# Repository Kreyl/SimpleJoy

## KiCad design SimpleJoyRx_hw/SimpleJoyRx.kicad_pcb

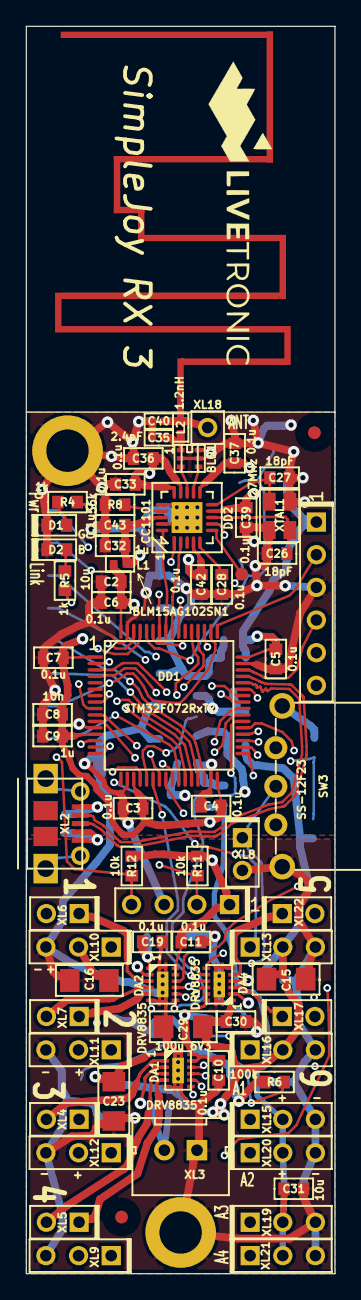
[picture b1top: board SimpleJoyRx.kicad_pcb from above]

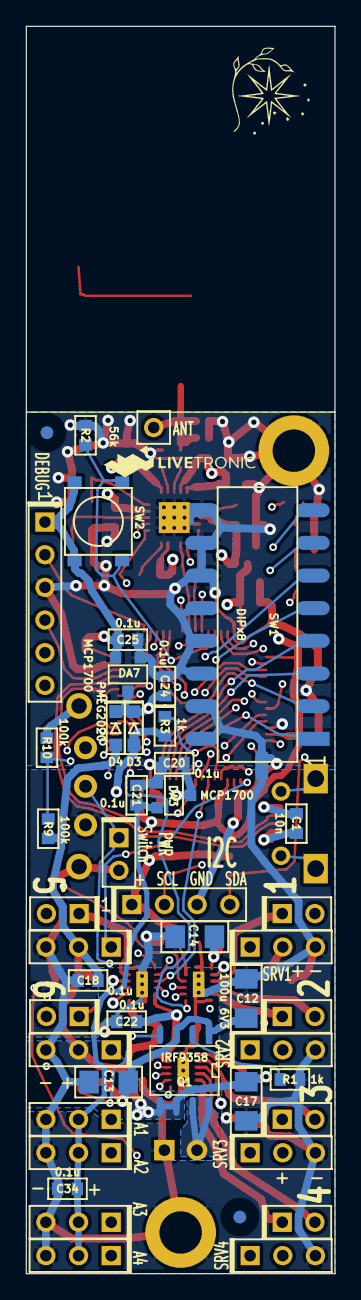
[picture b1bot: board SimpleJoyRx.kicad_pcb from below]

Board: 4 copper layers, 24.0 x 97.0 mm, 105 parts (29 on the bottom side), 82 nets.

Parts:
ANT1: ANT_PCB_MONO; ANT_868_24x30
BLN1: BALUN868JOHANSON; BALUN_JOHANSON868
C1, C8: 10n; CAP_0603
C2, C31: 10u; CAP_0603
C3, C4, C5, C6, C7, C10, C11, C18, C19, C20, C21, C22, C24, C25, C28, C30, C33, C34, C36, C37, C39, C42, C43: 0.1u; CAP_0603
C9, C32: 1u; CAP_0603
C12, C13, C14, C15, C16, C17, C23, C29: 100u 6V3; CAP_1206
C26, C27: 18pF; CAP_0603
C35: 2.4pF; CAP_0402
C40: DoNotMount; CAP_0402
D1: L-C191KGCT; LED_0603
D2: L-C191LBCT; LED_0603
D3, D4: PMEG2020; SOD323
DA1, DA2, DA4: DRV8835; WSON12
DA3, DA7: MCP1700; SOT23-3A
DD1: STM32F072RxTx; LQFP64
DD2: CC1101; QFN20
F1: Fuse0R; FuseShorted
HOLE1, HOLE2: HOLE_METALLED; Hole3d3_out5d5mm
L1: BLM15AG102SN1; IND_0402
L2: 1.2nH; IND_0402
Logo1: Logo; Ostranna_8x8
Logo2: Logo; Livetronic27x9
Logo3: Logo; Livetronic13x4
Q1: IRF9358; SO8_150MIL
R1, R3, R4, R5: 1k; RES_0603
R2, R8: 56k; RES_0603
R6, R9, R10: 100k; RES_0603
R11, R12: 10k; RES_0603
RP1, RP2, RP3, RP4: REFPOINT; REF_POINT_1MM
SW1: DIPx8; DIP_SMD_X8
SW2: IT-1187A; BTN_4x4_SMD
SW3: SS-12F23; SW_SS-12F23
TP1: TESTPOINT; TESTPOINT_1MM
XL1: CONN_6; PLS-6
XL2: USB_MICRO; USBmicro_MOLEX_1050170001
XL3: CONN_2; W02_Pitch_2d54
XL4, XL5, XL6, XL7, XL8, XL17, XL22: PLS2; PLS-2
XL9, XL10, XL11, XL12, XL13, XL15, XL16, XL19, XL20, XL21: PLS3; PLS-3
XL14: CONN_4; PLS-4
XL18: CONN_1; PLS-1Rnd
XTAL1: 27MHz; 03225C4

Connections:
+3.3V: C2.1, C3.1, C4.1, C5.1, C6.1, C7.1, C8.1, C9.1, C10.2, C11.2, C22.2, C25.1, DA1.11, DA1.12, DA2.11, DA2.12, DA4.11, DA4.12, DA7.2, DD1.1, DD1.13, DD1.19, DD1.32, DD1.48, DD1.64, L1.2, R11.1, R12.1, SW2.2, XL1.1, XL14.1
+BATT: C12.2, C13.2, Q1.1, Q1.3, R6.2
/5V_USB: C1.2, D3.A, R3.1, XL2.1
/A1: DD1.10, XL15.1
/A2: DD1.11, XL20.1
/A3: DD1.24, XL19.1
/A4: DD1.25, XL21.1
/ANT1: BLN1.1, C35.1, L2.2
/ANT2: ANT1.1, C40.1, L2.1, XL18.1
/BAT_MEAS: DD1.14, R9.1, R10.2
/CC_CS: DD1.28, DD2.7
/CC_GDO0: DD1.27, DD2.6, TP1.1
/CC_MISO: DD1.56, DD2.2
/CC_MOSI: DD1.57, DD2.20
/CC_SCK: DD1.55, DD2.1
/D+: DD1.45, XL2.3
/D-: DD1.44, XL2.2
/DIP1: DD1.26, SW1.1
/DIP2: DD1.50, SW1.2
/DIP3: DD1.29, SW1.3
/DIP4: DD1.30, SW1.4
/DIP5: DD1.33, SW1.5
/DIP6: DD1.34, SW1.6
/DIP7: DD1.35, SW1.7
/DIP8: DD1.36, SW1.8
/DIR1: DA2.10, DD1.51
/DIR2: DA2.8, DD1.52
/DIR3: DA1.10, DD1.53
/DIR4: DA1.8, DD1.2
/DIR5: DA4.10, DD1.3
/DIR6: DA4.8, DD1.4
/MCU_PWR: C20.1, C24.1, D3.C, D4.C, DA3.3, DA7.3
/MOTORA1: DA2.2, XL6.2
/MOTORA2: DA2.3, XL6.1
/MOTORB1: DA2.4, XL7.2
/MOTORB2: DA2.5, XL7.1
/MOTORC1: DA1.2, XL4.2
/MOTORC2: DA1.3, XL4.1
/MOTORD1: DA1.4, XL5.2
/MOTORD2: DA1.5, XL5.1
/MOTORE1: DA4.2, XL17.2
/MOTORE2: DA4.3, XL17.1
/MOTORF1: DA4.4, XL22.2
/MOTORF2: DA4.5, XL22.1
/PRE_BAT_PWR: Q1.7, Q1.8, XL3.2
/PWM1: DA2.9, DD1.37
/PWM2: DA2.7, DD1.38
/PWM3: DA1.9, DD1.39
/PWM4: DA1.7, DD1.40
/PWM5: DA4.9, DD1.22
/PWM6: DA4.7, DD1.23
/RF1: BLN1.4, DD2.12
/RF2: BLN1.3, DD2.13
/SCL: DD1.61, R11.2, XL14.2
/SDA: DD1.62, R12.2, XL14.4
/SRV1: DD1.41, XL10.1
/SRV2: DD1.42, XL11.1
/SRV3: DD1.43, XL12.1
/SRV4: DD1.16, XL9.1
/SRV5: DD1.17, XL13.1
/SRV6: DD1.20, XL16.1
/SWCLK: DD1.49, XL1.2
/SWDIO: DD1.46, XL1.4
/UART_RX: DD1.59, XL1.6
/UART_TX: DD1.58, XL1.5
GND: BLN1.2, BLN1.5, BLN1.6, C1.1, C2.2, C3.2, C4.2, C5.2, C6.2, C7.2, C8.2, C9.2, C20.2, C21.2, C24.2, C25.2, C26.2, C27.2, C28.1, C32.1, C33.2, C35.2, C36.2, C37.2, C39.2, C40.2, C42.2, C43.2, D1.C, D2.C, DA3.1, DA7.1, DD1.12, DD1.18, DD1.31, DD1.47, DD1.63, DD2.16, DD2.19, DD2.PAD, F1.1, HOLE1.H, R2.2, R8.2, SW1.9, SW1.10, SW1.11, SW1.12, SW1.13, SW1.14, SW1.15, SW1.16, XL1.3, XL2.4, XL2.5, XL14.3, XTAL1.H
GNDPWR: C10.1, C11.1, C12.1, C13.1, C14.1, C15.1, C16.1, C17.1, C18.1, C19.1, C22.1, C23.1, C29.1, C30.1, C31.2, C34.1, DA1.6, DA1.PAD, DA2.6, DA2.PAD, DA4.6, DA4.PAD, F1.2, HOLE2.H, R1.2, R10.1, SW3.1, SW3.H, XL3.1, XL8.2, XL9.3, XL10.3, XL11.3, XL12.3, XL13.3, XL15.3, XL16.3, XL19.3, XL20.3, XL21.3
unnamed: C26.1, DD2.8, XTAL1.1
unnamed: C27.1, DD2.10, XTAL1.2
unnamed: C28.2, DD2.5
unnamed: D1.A, R4.1
unnamed: D2.A, R5.1
unnamed: DD1.8, R4.2
unnamed: DD1.9, R5.2
unnamed: DD1.21, R3.2
unnamed: DD1.60, R2.1, SW2.1
unnamed: DD2.17, R8.1
unnamed: Q1.2, R1.1
unnamed: Q1.4, R6.1, SW3.2, XL8.1
PwrUnst: C14.2, C15.2, C16.2, C17.2, C18.2, C19.2, C23.2, C29.2, C30.2, D4.A, DA1.1, DA2.1, DA4.1, Q1.5, Q1.6, R9.2, XL9.2, XL10.2, XL11.2, XL12.2, XL13.2, XL16.2
VAA: C21.1, C31.1, C34.2, DA3.2, XL15.2, XL19.2, XL20.2, XL21.2
VCC: C32.2, C33.1, C36.1, C37.1, C39.1, C42.1, C43.1, DD2.4, DD2.9, DD2.11, DD2.14, DD2.15, DD2.18, L1.1

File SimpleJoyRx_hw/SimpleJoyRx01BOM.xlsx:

Reference | Value | Footprint | Quantity | SolderPoints | Price | PN | URL | Info | SolderPointsDip | Color | Sum
ANT1 | ANT_PCB_MONO | Radio:ANT_868_24x30 | 1 | 0 | 0
BLN1 | BALUN868JOHANSON | Radio:BALUN_JOHANSON868 | 1 | 6 | 45 | 0896BM15A0001E | http://onelec.ru/products/0896bm15a0001e-52ab3408-7c12-4b8c-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
C2 | 10u | Capacitors:CAP_0603 | 1 | 2 | 4
C26 C27 | 18pF | Capacitors:CAP_0603 | 2 | 2 | 0.5
C10 C11 C18 C19 C20 C21 C24 C25 C28 C3 C31 C33 C36 C37 C39 C4 C41 C42 C43 C5 C6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 | 0.1u | Capacitors:CAP_0603 | 22 | 2 | 0.5
C35 | 2.4pF | Capacitors:CAP_0402 | 1 | 2 | 0.5
C12 C13 C14 C15 C16 C17 C30 C38 | 100u 6V3 | Capacitors:CAP_1206 | 8 | 2 | 7 | CL31A107MQHNNNE
C40 | DoNotMount | Capacitors:CAP_0402 | 1 | 2 | 0.5
C1 C8 | 10n | Capacitors:CAP_0603 | 2 | 2 | 0.5
C32 C9 | 1u | Capacitors:CAP_0603 | 2 | 2 | 0.5
D1 | L-C191KGCT | LEDs:LED_0603 | 1 | 2 | 2.2000000000000002 | L-C191KGCT | http://onelec.ru/products/l-c191kgct |  |  | Green
D2 | L-C191LBCT | LEDs:LED_0603 | 1 | 2 | 2.4 | L-C191LBCT | http://onelec.ru/products/l-c191lbct |  |  | Blue
D3 D4 D5 D6 | PMEG2020 | Diodes:SOD323 | 4 | 2 | 5.5 | PMEG2020EJ.115 | https://www.terraelectronica.ru/catalog_info.php?CODE=192057 | 2A 20V Vf=525mV
DA1 DA2 | DRV8835 | QFN_DFN:WSON12 | 2 | 13 | 95 | DRV8835DSSR | http://onelec.ru/products/drv8835dssr
DA3 DA7 | MCP1700 | SOT:SOT23-3A | 2 | 3 | 20 | MCP1700T-3302E/TT
DD1 | STM32F072RxTx | LQFP_TQFP:LQFP64 | 1 | 64 | 170 | stm32f072R8t6 | http://
DD2 | CC1101 | QFN_DFN:QFN20 | 1 | 21 | 140 |  | http://
F1 | Fuse0R | PCB:FuseShorted | 1 | 1 | 0
HOLE1 HOLE2 | HOLE_METALLED | PCB:Hole3d3_out5d5mm | 2 | 0 | 0
L1 | BLM15AG102SN1 | Inductors:IND_0402 | 1 | 2 | 1
L2 | 1.2nH | Inductors:IND_0402 | 1 | 2 | 4
Logo1 | Logo | Pictures:Ostranna_8x8 | 1 | 0 | 0
Logo2 | Logo | Pictures:Livetronic27x9 | 1 | 0 | 0
Logo3 | Logo | Pictures:Livetronic13x4 | 1 | 0 | 0
Q1 | IRF9358 | SO_DIL_TSSOP:SO8_150MIL | 1 | 8 | 29 |  | http://onelec.ru/products/irf9358pbf-dd012426-33d8-429e-9c6a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
Q2 | 2N7002 | SOT:SOT23-3 | 1 | 3 | 1.6
Q3 Q4 | IRLML0030 | SOT:SOT23-3 | 2 | 3 | 7.5 | IRLML0030TRPBF | https://www.terraelectronica.ru/catalog.php?ID=349&search=irlml0030
R1 R3 R4 R5 | 1k | Resistors:RES_0603 | 4 | 2 | 0.5
R10 R6 R7 R9 | 100k | Resistors:RES_0603 | 4 | 2 | 0.5
R11 R12 R2 R8 | 56k | Resistors:RES_0603 | 4 | 2 | 0.5
RP1 RP2 RP3 RP4 | REFPOINT | PCB:REF_POINT_1MM | 4 | 0 | 0
SW1 | DIPx8 | BtnsSwitches:DIP_SMD_X8 | 1 | 16 | 27 |  | http://www.zip-2002.ru/kommutatsiya/dip_pereklyuchateli/7128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
SW2 | IT-1187A | BtnsSwitches:BTN_4x4_SMD | 1 | 4 | 4 | IT-1187A
SW3 | 1P2T | BtnsSwitches:SW_SS-1P2T | 1 | 3 | 10
TP1 | TESTPOINT | PCB:TESTPOINT_1MM | 1 | 0 | 0
U1 | USBLC6 | SOT:SOT23-6 | 1 | 6 | 9 | USBLC6-2SC6 | https://www.terraelectronica.ru/catalog_info.php?CODE=244787
XL1 | CONN_6 | Connectors:PLS-6 | 1 | 6 | 1
XL10 XL11 XL12 XL13 XL15 XL16 XL19 XL20 XL21 XL9 | PLS3 | Connectors:PLS-3 | 10 | 3 | 1
XL14 XL17 XL4 XL5 XL6 XL7 XL8 | PLS2 | Connectors:PLS-2 | 7 | 2 | 0.5 |  |  |  | 2
XL18 | CONN_1 | Connectors:PLS-1Rnd | 1 | 0 | 0
XL2 | USB_MICRO | Connectors:USBmicro_MOLEX_1050170001 | 1 | 9 | 46 | 47491-0001
XL3 | CONN_2 | Connectors:W02_Pitch_2d54 | 1 | 2 | 2
XTAL1 | 27MHz | Quartz:03225C4 | 1 | 4 | 15
Печатная плата |  |  | 1 |  | 155 | 155
 |  |  | Итого | 209 |  | 155

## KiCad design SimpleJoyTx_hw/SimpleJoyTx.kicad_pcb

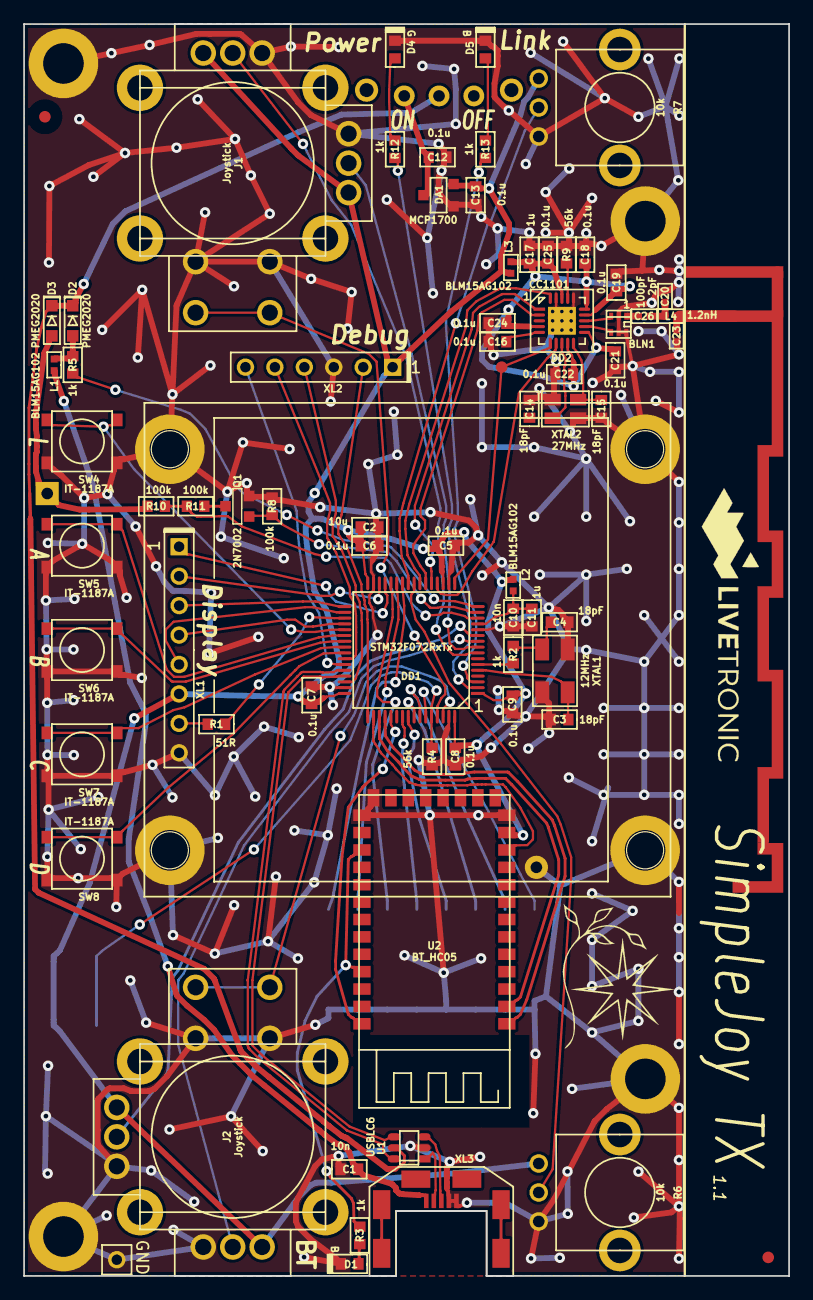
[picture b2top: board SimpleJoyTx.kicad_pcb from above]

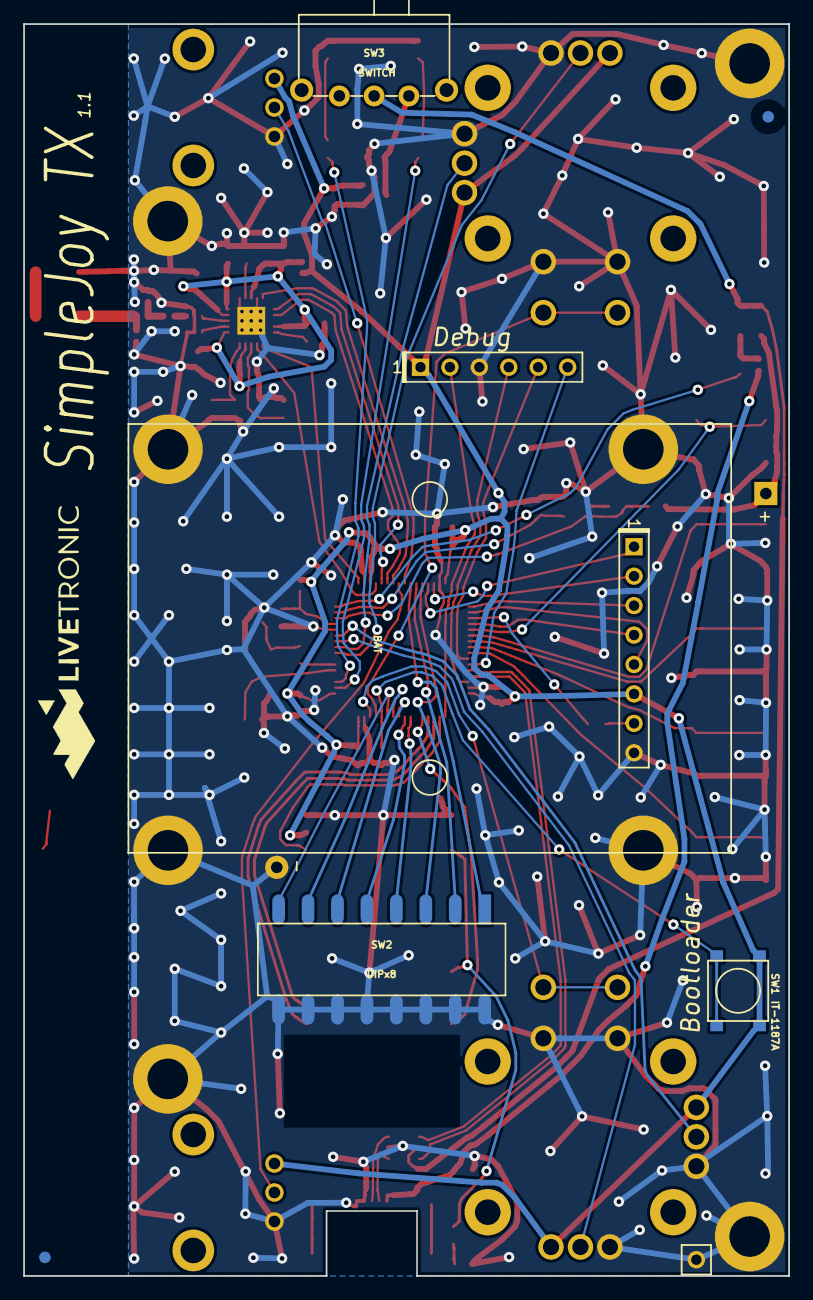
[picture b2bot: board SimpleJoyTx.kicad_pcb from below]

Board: 2 copper layers, 66.0 x 108.0 mm, 89 parts (7 on the bottom side), 77 nets.

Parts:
ANT1: ANT_PCB_MONO_2PIN; ANT_868_IFA_SIMPLEJOY
B1: BAT; BATTERY_AAA_X3
BLN1: BALUN868JOHANSON; BALUN_JOHANSON868
C1, C10: 10n; CAP_0603
C2: 10u; CAP_0603
C3, C4, C14, C15: 18pF; CAP_0603
C5, C6, C7, C8, C9, C12, C13, C16, C18, C19, C21, C22, C24, C25: 0.1u; CAP_0603
C11, C17: 1u; CAP_0603
C20: 2pF; CAP_0402
C23: DoNotMount; CAP_0402
C26: 100pF; CAP_0402
D1, D5: L-C191LBCT; LED_0603
D2, D3: PMEG2020; SOD323
D4: L-C191KGCT; LED_0603
DA1: MCP1700; SOT23-3A
DD1: STM32F072RxTx; LQFP64
DD2: CC1101; QFN20
HOLE1, HOLE2, HOLE3, HOLE4, HOLE5, HOLE6, HOLE7, HOLE8: HOLE_METALLED; Hole3_5_out6mm
J1, J2: Joystick
L1, L2, L3: BLM15AG102; IND_0402
L4: 1.2nH; IND_0402
Logo1: Logo; Ostranna_12d7_10d1
Logo2, Logo3: Logo; Livetronic27x9
Q1: 2N7002; SOT23-3
R1: 51R; RES_0603
R2, R3, R5, R12, R13: 1k; RES_0603
R4, R9: 56k; RES_0603
R6, R7: 10k; VAR_PTV09A-4
R8, R10, R11: 100k; RES_0603
RP1, RP2, RP3, RP4: REFPOINT; REF_POINT_1MM
SW1, SW4, SW5, SW6, SW7, SW8: IT-1187A; BTN_4x4_SMD
SW2: DIPx8; DIP_SMD_X8
SW3: SWITCH; SW_SS-12F23
TP1: TESTPOINT; TESTPOINT_1MM
U1: USBLC6; SOT23-6
U2: BT_HC05; BT_HC0x
XL1: PBS-8; PLS-8
XL2: CONN_6; PLS-6
XL3: USB_MINI_B; USBmicro_MOLEX_WM17142
XL4: CONN_1; PLS-1Rnd
XTAL1: 12MHz; 0503x4-4
XTAL2: 27MHz; 03225C4

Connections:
+3.3V: C2.1, C5.1, C6.1, C7.1, C8.1, C9.1, C13.1, DA1.2, DD1.1, DD1.19, DD1.32, DD1.48, DD1.64, J1.4, J1.10, J2.4, J2.10, L2.1, L3.2, R6.1, R7.1, SW1.2, U2.12, XL1.6, XL2.1
+5V: D2.A, L1.1, R5.1
+BATT: B1.A, D3.A, R10.2
/5V_USB: C1.2, L1.2, XL3.1
/ADC0: DD1.8, J1.9
/ADC1: DD1.9, J1.5
/ADC2: DD1.10, J2.9
/ADC3: DD1.11, J2.5
/ADC4: DD1.24, R6.3
/ADC5: DD1.25, R7.3
/ANT1: C20.1, C26.1, L4.2
/ANT2: ANT1.1, C23.1, L4.1
/BAT_MEAS: DD1.14, R10.1, R11.2
/BTN_A: DD1.38, SW5.1
/BTN_B: DD1.39, SW6.1
/BTN_C: DD1.40, SW7.1
/BTN_D: DD1.41, SW8.1
/BTN_J1: DD1.61, J1.1, J1.14
/BTN_J2: DD1.62, J2.1, J2.14
/BTN_L: DD1.37, SW4.1
/BT_PIO11: DD1.53, U2.34
/BT_RESET: DD1.50, U2.11
/CC_CS: DD1.20, DD2.7
/CC_GDO0: DD1.17, DD2.6, TP1.1
/CC_MISO: DD1.22, DD2.2
/CC_MOSI: DD1.23, DD2.20
/CC_SCK: DD1.21, DD2.1
/D+: DD1.45, U1.4
/D-: DD1.44, U1.6
/DIP1: DD1.26, SW2.1
/DIP2: DD1.27, SW2.2
/DIP3: DD1.28, SW2.3
/DIP4: DD1.55, SW2.4
/DIP5: DD1.56, SW2.5
/DIP6: DD1.57, SW2.6
/DIP7: DD1.58, SW2.7
/DIP8: DD1.59, SW2.8
/D_IN+: U1.3, XL3.3
/D_IN-: U1.1, XL3.2
/LCD_BCKLT: DD1.35, R1.1
/LCD_CE: DD1.30, XL1.2
/LCD_CLK: DD1.34, XL1.5
/LCD_DC: DD1.33, XL1.3
/LCD_DIN: DD1.36, XL1.4
/LCD_RST: DD1.29, XL1.1
/MCURX_BTTX: DD1.52, U2.1
/MCUTX_BTRX: DD1.51, U2.2
/MEASURE_EN: DD1.15, Q1.1, R8.2
/PWR_UNST_ALWAYS: D2.C, D3.C, SW3.2, U1.5
/RF1: BLN1.4, DD2.12
/RF2: BLN1.3, DD2.13
/SWCLK: DD1.49, XL2.2
/SWDIO: DD1.46, XL2.4
/UART_RX: DD1.43, XL2.6
/UART_TX: DD1.42, XL2.5
GND: ANT1.2, B1.C, BLN1.2, BLN1.5, BLN1.6, C1.1, C2.2, C3.2, C4.2, C5.2, C6.2, C7.2, C8.2, C9.2, C10.2, C11.2, C12.2, C13.2, C14.2, C15.2, C16.1, C17.2, C18.2, C19.2, C20.2, C21.2, C22.2, C23.2, C24.2, C25.2, D1.C, D4.C, D5.C, DA1.1, DD1.12, DD1.18, DD1.31, DD1.47, DD1.63, DD2.16, DD2.19, DD2.PAD, HOLE1.H, HOLE2.H, HOLE3.H, HOLE4.H, HOLE5.H, HOLE6.H, HOLE7.H, HOLE8.H, J1.2, J1.6, J1.8, J1.13, J2.2, J2.6, J2.8, J2.13, Q1.2, R4.2, R6.2, R7.2, R8.1, R9.2, SW2.9, SW2.10, SW2.11, SW2.12, SW2.13, SW2.14, SW2.15, SW2.16, SW4.2, SW5.2, SW6.2, SW7.2, SW8.2, U1.2, U2.13, U2.21, U2.22, XL1.8, XL2.3, XL3.4, XL3.5, XL4.1, XTAL1.H, XTAL2.H
unnamed: BLN1.1, C26.2
unnamed: C3.1, DD1.5, XTAL1.1
unnamed: C4.1, R2.1, XTAL1.2
unnamed: C10.1, C11.1, DD1.13, L2.2
unnamed: C14.1, DD2.8, XTAL2.1
unnamed: C15.1, DD2.10, XTAL2.2
unnamed: C16.2, DD2.5
unnamed: D1.A, R3.1
unnamed: D4.A, R12.1
unnamed: D5.A, R13.1
unnamed: DD1.2, R12.2
unnamed: DD1.3, R13.2
unnamed: DD1.6, R2.2
unnamed: DD1.16, R5.2
unnamed: DD1.60, R4.1, SW1.1
unnamed: DD2.17, R9.1
unnamed: Q1.3, R11.1
unnamed: R1.2, XL1.7
unnamed: R3.2, U2.24, U2.31
PwrUnst: C12.1, DA1.3, SW3.1
VCC: C17.1, C18.1, C19.1, C21.1, C22.1, C24.1, C25.1, DD2.4, DD2.9, DD2.11, DD2.14, DD2.15, DD2.18, L3.1

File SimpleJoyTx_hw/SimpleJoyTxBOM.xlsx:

Reference | Value | Footprint | Quantity | SolderPoints | Price | Sum | PN | URL | Color
ANT1 | ANT_PCB_MONO_2PIN | Radio:ANT_868_IFA_SIMPLEJOY | 1 | 0 | 0 | 0
B1 | BAT | Installation:BATTERY_AAA_X3 | 1 | 2 | 30 | 30 |  | http://www.quartz1.com/price/model.php?akt=5470.11
BLN1 | BALUN868JOHANSON | Radio:BALUN_JOHANSON868 | 1 | 6 | 45 | 45 | 0896BM15A0001E | http://onelec.ru/products/0896bm15a0001e-52ab3408-7c12-4b8c-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
C1 C10 | 10n | Capacitors:CAP_0603 | 2 | 2 | 0.5 | 1
C11 C17 | 1u | Capacitors:CAP_0603 | 2 | 2 | 0.5 | 1
C14 C15 C3 C4 | 18pF | Capacitors:CAP_0603 | 4 | 2 | 0.5 | 2
C12 C13 C16 C18 C19 C21 C22 C24 C25 C5 C6 C7 C8 C9 | 0.1u | Capacitors:CAP_0603 | 14 | 2 | 0.5 | 7
C2 | 10u | Capacitors:CAP_0603 | 1 | 2 | 4 | 4
C20 | 2pF | Capacitors:CAP_0402 | 1 | 2 | 0.5 | 0.5
C23 | DoNotMount | Capacitors:CAP_0402 | 1 | 2 | 0.5 | 0.5
D1 D5 | L-C191LBCT | LEDs:LED_0603 | 2 | 2 | 2.4 | 4.8 | L-C191LBCT | http://onelec.ru/products/l-c191lbct | Blue
D2 D3 | PMEG2020 | Diodes:SOD323 | 2 | 2 | 5 | 10
D4 | L-C191KGCT | LEDs:LED_0603 | 1 | 2 | 2.2000000000000002 | 2.2000000000000002 | L-C191KGCT | http://onelec.ru/products/l-c191kgct | Green
DA1 | MCP1700 | SOT:SOT23-3 | 1 | 3 | 20 | 20 | MCP1700T-3302E/TT
DD1 | STM32F072RxTx | LQFP_TQFP:LQFP64 | 1 | 64 | 170 | 170 | stm32f072R8t6 | http://
DD2 | CC1101 | QFN_DFN:QFN20 | 1 | 21 | 140 | 140 |  | http://
HOLE1 HOLE2 HOLE3 HOLE4 HOLE5 HOLE6 HOLE7 HOLE8 | HOLE_METALLED | PCB:Hole3_5_out6mm | 8 | 0 | 0 | 0
J1 J2 | Joystick | BtnsSwitches:Joystick | 2 | 14 | 35 | 70 |  | https://ru.aliexpress.com/item/2pcs-3D-Controller-Joystick-A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
L1 L2 L3 | BLM15AG102 | Inductors:IND_0402 | 3 | 2 | 1 | 3 | BLM15AG102SN1
L4 | 1.2nH | Inductors:IND_0402 | 1 | 2 | 4 | 4
Logo1 | Logo | Pictures:Ostranna_12d7_10d1 | 1 | 0 | 0 | 0
Logo2 Logo3 | Logo | Pictures:Livetronic27x9 | 2 | 0 | 0 | 0
Q1 | 2N7002 | SOT:SOT23-3 | 1 | 3 | 1.6 | 1.6
R1 | 51R | Resistors:RES_0603 | 1 | 2 | 0.5 | 0.5
R12 R13 R2 R3 R5 | 1k | Resistors:RES_0603 | 5 | 2 | 0.5 | 2.5
R4 R9 | 56k | Resistors:RES_0603 | 2 | 2 | 0.5 | 1
R6 R7 | 10k | Resistors:VAR_PTV09A-4 | 2 | 5 | 11 | 22 |  | http://www.zip-2002.ru/rezistory/potentsiometry/69732/rs09-n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
R10 R11 R8 | 100k | Resistors:RES_0603 | 3 | 2 | 0.5 | 1.5
RP1 RP2 RP3 RP4 | REFPOINT | PCB:REF_POINT_1MM | 4 | 0 | 0 | 0
SW2 | DIPx8 | BtnsSwitches:DIP_SMD_X8 | 1 | 16 | 35 | 35 | 1-1825058-9 | https://www.terraelectronica.ru/catalog_info.php?CODE=854801
SW3 | SWITCH | BtnsSwitches:SW_SS-12F23 | 1 | 5 | 5 | 5
SW1 SW4 SW5 SW6 SW7 SW8 | IT-1187A | BtnsSwitches:BTN_4x4_SMD | 6 | 4 | 4 | 24 |  | http://www.zip-2002.ru/kommutatsiya/taktovye_knopki/83335/it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
TP1 | TESTPOINT | PCB:TESTPOINT_1MM | 1 | 0 | 0 | 0
U1 | USBLC6 | SOT:SOT23-6 | 1 | 6 | 9 | 9 | USBLC6-2SC6 | https://www.terraelectronica.ru/catalog_info.php?CODE=244787
U2 | BT_HC05 | Modules:BT_HC0x | 1 | 34 |  | 0
XL1 | PBS-8 | Connectors:PLS-8 | 1 | 8 | 24 | 24 |  | http://www.quartz1.com/price/model.php?group=1136&ext=1932
XL2 | CONN_6 | Connectors:PLS-6 | 1 | 6 | 2 | 2
XL3 | USB_MINI_B | Connectors:USBmicro_MOLEX_WM17142 | 1 | 9 | 46 | 46 | 47491-0001
XL4 | CONN_1 | Connectors:PLS-1Rnd | 1 | 0 | 0 | 0
XTAL1 | 12MHz | Quartz:0503x4-4 | 1 | 4 | 15 | 15
XTAL2 | 27MHz | Quartz:03225C4 | 1 | 4 | 15 | 15
Печатная плата |  |  |  |  |  | 250
 |  |  | Итого | 246 |  | 939.1

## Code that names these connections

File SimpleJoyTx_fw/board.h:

/*
 * board.h
 *
 *  Created on: 01.02.2017
 *      Author: Kreyl
 */

#pragma once

// ==== General ====
#define BOARD_NAME          "SimpleJoyTx1"
#define APP_NAME            "SimpleJoyTx"

// MCU type as defined in the ST header.
#define STM32F072xB     // no matter, 8 or B

// Freq of external crystal if any. Leave it here even if not used.
#define CRYSTAL_FREQ_HZ         12000000

// Ch timer
#define STM32_ST_IRQ_PRIORITY   2
#define STM32_ST_USE_TIMER      2
#define STM32_TIMCLK1           (Clk.APBFreqHz)

#define SIMPLESENSORS_ENABLED   TRUE
#define BUTTONS_ENABLED         TRUE
#define ADC_REQUIRED            TRUE
#define I2C1_ENABLED            FALSE
#define I2C_USE_SEMAPHORE       FALSE

// ADC timer
#define ADC_TIM                 TIM1

#if 1 // ========================== GPIO =======================================
// PortMinTim_t: GPIO, Pin, Tim, TimChnl, invInverted, omPushPull, TopValue

// Battery measurement
#define BAT_MEAS_PIN    GPIOA, 1

// Buttons
#define BTN_A_PIN       GPIOC, 7, pudPullUp
#define BTN_B_PIN       GPIOC, 8, pudPullUp
#define BTN_C_PIN       GPIOC, 9, pudPullUp
#define BTN_D_PIN       GPIOA, 8, pudPullUp
#define BTN_L_PIN       GPIOC, 6, pudPullUp
#define BTN_J1_PIN      GPIOB, 8, pudPullUp
#define BTN_J2_PIN      GPIOB, 9, pudPullUp

// LED RGB
#define LED_B_PIN       { GPIOB, 1, TIM3, 4, invNotInverted, omPushPull, 255 }
#define LED_R_PIN       { GPIOB, 0, TIM3, 3, invNotInverted, omPushPull, 255 }
#define LED_G_PIN       { GPIOB, 4, TIM3, 1, invNotInverted, omPushPull, 255 }
// LEDs
#define LED_PWR         GPIOC, 13, omPushPull
#define LED_LINK        GPIOC, 14, omPushPull

// UART
#define UART_GPIO       GPIOA
#define UART_TX_PIN     9
#define UART_RX_PIN     10

// USB
#define USB_DETECT_PIN  GPIOA, 2
#define USB_DM          GPIOA, 11
#define USB_DP          GPIOA, 12

// Bluetooth
#define BT_RST_PIN      GPIOA, 15, omPushPull
#define BTRX_MCUTX      GPIOC, 10
#define BTTX_MCURX      GPIOC, 11
#define BT_PIO11        GPIOC, 12

// DIP switch
#define DIP_SW_CNT      8
#define DIP_SW1         { GPIOB, 0, pudPullUp }
#define DIP_SW2         { GPIOB, 1, pudPullUp }
#define DIP_SW3         { GPIOB, 2, pudPullUp }
#define DIP_SW4         { GPIOB, 3, pudPullUp }
#define DIP_SW5         { GPIOB, 4, pudPullUp }
#define DIP_SW6         { GPIOB, 5, pudPullUp }
#define DIP_SW7         { GPIOB, 6, pudPullUp }
#define DIP_SW8         { GPIOB, 7, pudPullUp }

// LCD
#define LCD_RST_PIN     GPIOB, 10
#define LCD_CE_PIN      GPIOB, 11
#define LCD_DC_PIN      GPIOB, 12
#define LCD_CLK_PIN     GPIOB, 13
#define LCD_BCKLT_PIN   {GPIOB, 14, TIM15, 1, invNotInverted, omPushPull, 100}
#define LCD_DIN_PIN     GPIOB, 15

// ADC
#define ADC0_PIN        GPIOC, 0, 10
#define ADC1_PIN        GPIOC, 1, 11
#define ADC2_PIN        GPIOC, 2, 12
#define ADC3_PIN        GPIOC, 3, 13
#define ADC4_PIN        GPIOC, 4, 14
#define ADC5_PIN        GPIOC, 5, 15

// Radio: SPI, PGpio, Sck, Miso, Mosi, Cs, Gdo0
#define CC_Setup0       SPI1, GPIOA, 5,6,7, GPIOA,4, GPIOA,3

#endif // GPIO

#define LCD_SPI         SPI2

#if 1 // ========================== USB ========================================
#define USBDrv          USBD1   // USB driver to use

// CRS
#define CRS_PRESCALER   RCC_CRS_SYNC_DIV1
#define CRS_SOURCE      RCC_CRS_SYNC_SOURCE_USB
#define CRS_POLARITY    RCC_CRS_SYNC_POLARITY_RISING
#define CRS_RELOAD_VAL  ((48000000 / 1000) - 1) // Ftarget / Fsync - 1
#define CRS_ERROR_LIMIT 34
#define HSI48_CALIBRATN 32
#endif

#if 1 // =========================== DMA =======================================
#define STM32_DMA_REQUIRED  TRUE
// ==== Uart ====
#define UART_DMA_TX_MODE(Chnl) (STM32_DMA_CR_CHSEL(Chnl) | DMA_PRIORITY_LOW | STM32_DMA_CR_MSIZE_BYTE | STM32_DMA_CR_PSIZE_BYTE | STM32_DMA_CR_MINC | STM32_DMA_CR_DIR_M2P | STM32_DMA_CR_TCIE)
#define UART_DMA_RX_MODE(Chnl) (STM32_DMA_CR_CHSEL(Chnl) | DMA_PRIORITY_MEDIUM | STM32_DMA_CR_MSIZE_BYTE | STM32_DMA_CR_PSIZE_BYTE | STM32_DMA_CR_MINC | STM32_DMA_CR_DIR_P2M | STM32_DMA_CR_CIRC)
#define UART_DMA_TX     STM32_DMA_STREAM_ID(1, 2)
#define UART_DMA_RX     STM32_DMA_STREAM_ID(1, 3)
#define UART_DMA_CHNL   0   // Dummy

#define LCD_DMA         STM32_DMA_STREAM_ID(1, 5)

#if ADC_REQUIRED
#define ADC_DMA         STM32_DMA_STREAM_ID(1, 1)
#define ADC_DMA_MODE    STM32_DMA_CR_CHSEL(0) |   /* dummy */ \
                        DMA_PRIORITY_HIGH | \
                        STM32_DMA_CR_MSIZE_HWORD | \
                        STM32_DMA_CR_PSIZE_HWORD | \
                        STM32_DMA_CR_MINC |       /* Memory pointer increase */ \
                        STM32_DMA_CR_DIR_P2M |    /* Direction is peripheral to memory */ \
                        STM32_DMA_CR_TCIE         /* Enable Transmission Complete IRQ */
#endif // ADC

#endif // DMA

#if 1 // ========================== USART ======================================
#define PRINTF_FLOAT_EN FALSE
#define UART_TXBUF_SZ   2048
#define UART_RXBUF_SZ   512
#define CMD_BUF_SZ      256

#define CMD_UART        USART1


#define CMD_UART_PARAMS \
    CMD_UART, UART_GPIO, UART_TX_PIN, UART_GPIO, UART_RX_PIN, \
    UART_DMA_TX, UART_DMA_RX, UART_DMA_TX_MODE(UART_DMA_CHNL), UART_DMA_RX_MODE(UART_DMA_CHNL), \
    uartclkHSI // independent clock

#endif

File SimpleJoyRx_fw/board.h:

/*
 * board.h
 *
 *  Created on: 01.02.2017
 *      Author: Kreyl
 */

#pragma once

#include <inttypes.h>

// ==== General ====
#define BOARD_NAME          "SimpleJoyRx1"
#define APP_NAME            "Golocron"

// MCU type as defined in the ST header.
#define STM32F072xB     // no matter, 8 or B

// Freq of external crystal if any. Leave it here even if not used.
#define CRYSTAL_FREQ_HZ         12000000

#define SYS_TIM_CLK             (Clk.APBFreqHz)

#define SIMPLESENSORS_ENABLED   FALSE
#define BUTTONS_ENABLED         FALSE
#define ADC_REQUIRED            FALSE
#define I2C1_ENABLED            FALSE
#define I2C_USE_SEMAPHORE       FALSE

#if 1 // ========================== GPIO =======================================
// PortMinTim_t: GPIO, Pin, Tim, TimChnl, invInverted, omPushPull, TopValue

// Battery measurement
#define BAT_MEAS_PIN    GPIOA, 0

// Servo
#define SRV1_PIN        GPIOA, 8, TIM1, 1
#define SRV2_PIN        GPIOA, 9, TIM1, 2
#define SRV3_PIN        GPIOA, 10, TIM1, 3
#define SRV4_PIN        GPIOA, 2, TIM15, 1
#define SRV5_PIN        GPIOA, 3, TIM15, 2
#define SRV6_PIN        GPIOA, 4, TIM14, 1

#define USB_DETECT      GPIOA, 5

// PWM
#define PWM1_PIN        GPIOC, 6, TIM3, 1, invNotInverted, omPushPull, 255
#define PWM2_PIN        GPIOC, 7, TIM3, 2, invNotInverted, omPushPull, 255
#define PWM3_PIN        GPIOC, 8, TIM3, 3, invNotInverted, omPushPull, 255
#define PWM4_PIN        GPIOC, 9, TIM3, 4, invNotInverted, omPushPull, 255
#define PWM5_PIN        GPIOA, 6, TIM16, 1, invNotInverted, omPushPull, 255
#define PWM6_PIN        GPIOA, 7, TIM17, 1, invNotInverted, omPushPull, 255

// Motor Dir
#define DIR1_PIN        GPIOC, 10
#define DIR2_PIN        GPIOC, 11
#define DIR3_PIN        GPIOC, 12
#define DIR4_PIN        GPIOC, 13
#define DIR5_PIN        GPIOC, 14
#define DIR6_PIN        GPIOC, 15

// Analog pins
#define A1_PIN          GPIOC, 2
#define A2_PIN          GPIOC, 3
#define A3_PIN          GPIOC, 4
#define A4_PIN          GPIOC, 5

// USB
#define USB_DM          GPIOA, 11
#define USB_DP          GPIOA, 12

// LEDs
#define LED_PWR         GPIOC, 0, omPushPull
#define LED_LINK        GPIOC, 1, omPushPull

// Neopixel LEDs
#define NPX1_SPI        SPI2
#define NPX1_GPIO       GPIOB
#define NPX1_PIN        15
#define NPX1_AF         AF0

// UART
#define UART_GPIO       GPIOB
#define UART_TX_PIN     6
#define UART_RX_PIN     7

// I2C
#define I2C_SCL         GPIOB, 8
#define I2C_SDA         GPIOB, 9

// Radio: SPI, PGpio, Sck, Miso, Mosi, Cs, Gdo0
#define CC_Setup0       SPI1, GPIOB, 3,4,5, 2, 1

// DIP switch
#define DIP_SW_CNT      8
#define DIP_SW1         { GPIOB, 0, pudPullUp }
#define DIP_SW2         { GPIOA, 15, pudPullUp }
#define DIP_SW3         { GPIOB, 10, pudPullUp }
#define DIP_SW4         { GPIOB, 11, pudPullUp }
#define DIP_SW5         { GPIOB, 12, pudPullUp }
#define DIP_SW6         { GPIOB, 13, pudPullUp }
#define DIP_SW7         { GPIOB, 14, pudPullUp }
#define DIP_SW8         { GPIOB, 15, pudPullUp }

#endif // GPIO

#if 1 // ========================== USB ========================================
#define USBDrv          USBD1   // USB driver to use

// CRS
#define CRS_PRESCALER   RCC_CRS_SYNC_DIV1
#define CRS_SOURCE      RCC_CRS_SYNC_SOURCE_USB
#define CRS_POLARITY    RCC_CRS_SYNC_POLARITY_RISING
#define CRS_RELOAD_VAL  ((48000000 / 1000) - 1) // Ftarget / Fsync - 1
#define CRS_ERROR_LIMIT 34
#define HSI48_CALIBRATN 32
#endif

#if ADC_REQUIRED // ======================= Inner ADC ==========================
#define ADC_MEAS_PERIOD_MS  99
// Clock divider: clock is generated from the APB2
#define ADC_CLK_DIVIDER     adcDiv2

// ADC channels
#define ADC_A1_CHNL         12
#define ADC_A2_CHNL         13
#define ADC_A3_CHNL         14
#define ADC_A4_CHNL         15

#define ADC_VREFINT_CHNL    17  // All 4xx, F072 and L151 devices. Do not change.
#define ADC_CHANNELS        { ADC_A1_CHNL, ADC_A2_CHNL, ADC_A3_CHNL, ADC_A4_CHNL, ADC_VREFINT_CHNL }
#define ADC_CHANNEL_CNT     5   // Do not use countof(AdcChannels) as preprocessor does not know what is countof => cannot check
#define ADC_SAMPLE_TIME     ast55d5Cycles
#define ADC_SAMPLE_CNT      8   // How many times to measure every channel

#define ADC_SEQ_LEN         (ADC_SAMPLE_CNT * ADC_CHANNEL_CNT)

#endif

#if 1 // =========================== DMA =======================================
#define STM32_DMA_REQUIRED  TRUE
// ==== Uart ====
#define UART_DMA_TX     STM32_DMA1_STREAM2
#define UART_DMA_RX     STM32_DMA1_STREAM3
#define UART_DMA_CHNL   0   // Dummy
#define UART_DMA_TX_MODE(Chnl) (STM32_DMA_CR_CHSEL(Chnl) | DMA_PRIORITY_LOW | STM32_DMA_CR_MSIZE_BYTE | STM32_DMA_CR_PSIZE_BYTE | STM32_DMA_CR_MINC | STM32_DMA_CR_DIR_M2P | STM32_DMA_CR_TCIE)
#define UART_DMA_RX_MODE(Chnl) (STM32_DMA_CR_CHSEL(Chnl) | DMA_PRIORITY_MEDIUM | STM32_DMA_CR_MSIZE_BYTE | STM32_DMA_CR_PSIZE_BYTE | STM32_DMA_CR_MINC | STM32_DMA_CR_DIR_P2M | STM32_DMA_CR_CIRC)

#define NPX1_DMA        STM32_DMA1_STREAM5  // SPI2 TX
#define NPX1_DMA_CHNL   0 // Dummy

// ==== I2C1 ====
#define I2C1_DMA_TX     STM32_DMA1_STREAM2
#define I2C1_DMA_RX     STM32_DMA1_STREAM3
#define I2C1_DMA_CHNL   0 // Dummy

#if ADC_REQUIRED
#define ADC_DMA         STM32_DMA1_STREAM1
#define ADC_DMA_MODE    STM32_DMA_CR_CHSEL(0) |   /* dummy */ \
                        DMA_PRIORITY_LOW | \
                        STM32_DMA_CR_MSIZE_HWORD | \
                        STM32_DMA_CR_PSIZE_HWORD | \
                        STM32_DMA_CR_MINC |       /* Memory pointer increase */ \
                        STM32_DMA_CR_DIR_P2M |    /* Direction is peripheral to memory */ \
                        STM32_DMA_CR_TCIE         /* Enable Transmission Complete IRQ */
#endif // ADC

#endif // DMA

#if 1 // ========================== USART ======================================
#define PRINTF_FLOAT_EN FALSE
#define UART_TXBUF_SZ   1024
#define UART_RXBUF_SZ   99

#define UARTS_CNT       1

#define CMD_UART_PARAMS \
    USART1, UART_GPIO, UART_TX_PIN, UART_GPIO, UART_RX_PIN, \
    UART_DMA_TX, UART_DMA_RX, UART_DMA_TX_MODE(UART_DMA_CHNL), UART_DMA_RX_MODE(UART_DMA_CHNL), \
    true // Use independent clock

#endif

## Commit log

2017-09-27 + TZ
2017-10-03 TX sch started
2017-10-04 Proceeding with RX
2017-10-05 + TX sch RC
2017-10-05 + RX sch
2017-10-05 * DRV8835 for 4 channels
2017-10-07 RX PCB 2x5
2017-10-07 RX layout done
2017-10-09 Rx tracing done
2017-10-09 + Antenna
2017-10-09 RX PCB seems done
2017-10-09 TX layout started
2017-10-11 + Layout + antenna
2017-10-11 + SimpleJoy TX * Leg 63 bug fixed
2017-10-11 TX: USB and switch moved to edges. Sent to production.
2017-10-26 + rx fw
2017-10-26 + LEDs
2017-10-26 + DIP
2017-10-26 + Radio + PWM + Servo
2017-10-26 + Antennas matched
2017-10-27 + TX firmware, LEDs work
2017-10-31 + ADC & calibration
2017-10-31 + Btns in pkt + Sign corrected
2017-10-31 LCD generally works, but font is upside down
2017-10-31 Something wrong with Lcd.GotoXY
2017-11-01 LCD fixed
2017-11-01 LCD update ok
2017-11-01 Proceeding with grafic controls
2017-11-01 + R done Proceeding with joysticks
2017-11-02 + Y joysticks
2017-11-02 + Joysticks X * Switch to 48MHz
2017-11-02 + Backlight on\off
2017-11-02 + Show battery
2017-11-02 Minor changes
2017-11-02 Radio works
2017-11-03 + Radio
2017-11-03 + Srv + DC Motors
2017-11-03 + Radio level
2017-11-03 + USB serial works
2017-11-03 + USB control
2017-11-03 Motors off on link down for 5400 ms
2017-11-04 * LCD do not inverts on start
2017-11-05 + Logo display * Draw image invert bit order
2017-11-06 2s for logo
2017-12-04 + RX v2
2018-02-19 Proceeding
2018-04-27 * rPkt format changed * Rx v3 done Seems working
2018-07-11 Switch to Atollic
2018-07-11 Interface started
2018-07-11 + Mode switching
2018-07-13 + LED RGB
2018-07-13 Switch LED to hsv + flickering and color
2018-07-13 + Random flicker
2018-07-14 Switch to timer-driven LED
2018-07-14 Better flicker
2018-07-14 Alpha
2018-07-18 Minor
2018-08-15 Srv works
2018-09-04 Something
2022-06-04 Old data
2022-06-04 Sch switched to new KiCAD version
2022-06-04 + RX L476fw os
2022-06-04 + Tx Fw OS + Radio + Usb
2022-06-09 Rx/Tx works
